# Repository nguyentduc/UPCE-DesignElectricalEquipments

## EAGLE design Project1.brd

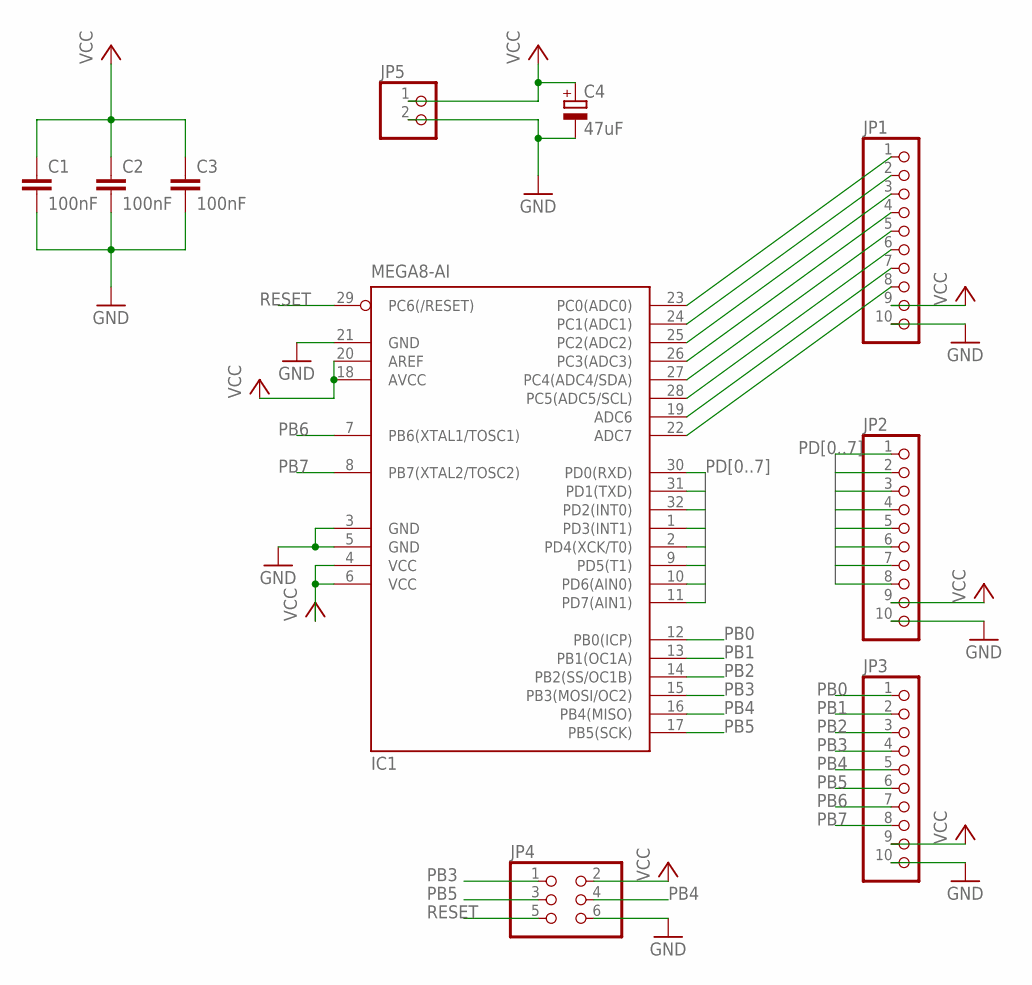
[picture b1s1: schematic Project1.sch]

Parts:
C1, C2, C3: 100nF; C0603
C4: 47uF; E2,5-6
IC1: MEGA8-AI; TQFP32-08
JP1, JP2, JP3: PINHD-1X10; 1X10
JP4: PINHD-2X3; 2X03
JP5: PINHD-1X2; 1X02

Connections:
GND: C1.2, C2.2, C3.2, C4.-, IC1.3 (GND), IC1.5 (GND), IC1.21 (GND), JP1.10, JP2.10, JP3.10, JP4.6, JP5.2
unnamed: IC1.23 (PC0(ADC0)), JP1.1
unnamed: IC1.24 (PC1(ADC1)), JP1.2
unnamed: IC1.25 (PC2(ADC2)), JP1.3
unnamed: IC1.26 (PC3(ADC3)), JP1.4
unnamed: IC1.27 (PC4(ADC4/SDA)), JP1.5
unnamed: IC1.28 (PC5(ADC5/SCL)), JP1.6
unnamed: IC1.19 (ADC6), JP1.7
unnamed: IC1.22 (ADC7), JP1.8
PB0: IC1.12 (PB0(ICP)), JP3.1
PB1: IC1.13 (PB1(OC1A)), JP3.2
PB2: IC1.14 (PB2(SS/OC1B)), JP3.3
PB3: IC1.15 (PB3(MOSI/OC2)), JP3.4, JP4.1
PB4: IC1.16 (PB4(MISO)), JP3.5, JP4.4
PB5: IC1.17 (PB5(SCK)), JP3.6, JP4.3
PB6: IC1.7 (PB6(XTAL1/TOSC1)), JP3.7
PB7: IC1.8 (PB7(XTAL2/TOSC2)), JP3.8
PD0: IC1.30 (PD0(RXD)), JP2.1
PD1: IC1.31 (PD1(TXD)), JP2.2
PD2: IC1.32 (PD2(INT0)), JP2.3
PD3: IC1.1 (PD3(INT1)), JP2.4
PD4: IC1.2 (PD4(XCK/T0)), JP2.5
PD5: IC1.9 (PD5(T1)), JP2.6
PD6: IC1.10 (PD6(AIN0)), JP2.7
PD7: IC1.11 (PD7(AIN1)), JP2.8
RESET: IC1.29 (PC6(/RESET)), JP4.5
VCC: C1.1, C2.1, C3.1, C4.+, IC1.4 (VCC), IC1.6 (VCC), IC1.18 (AVCC), IC1.20 (AREF), JP1.9, JP2.9, JP3.9, JP4.2, JP5.1

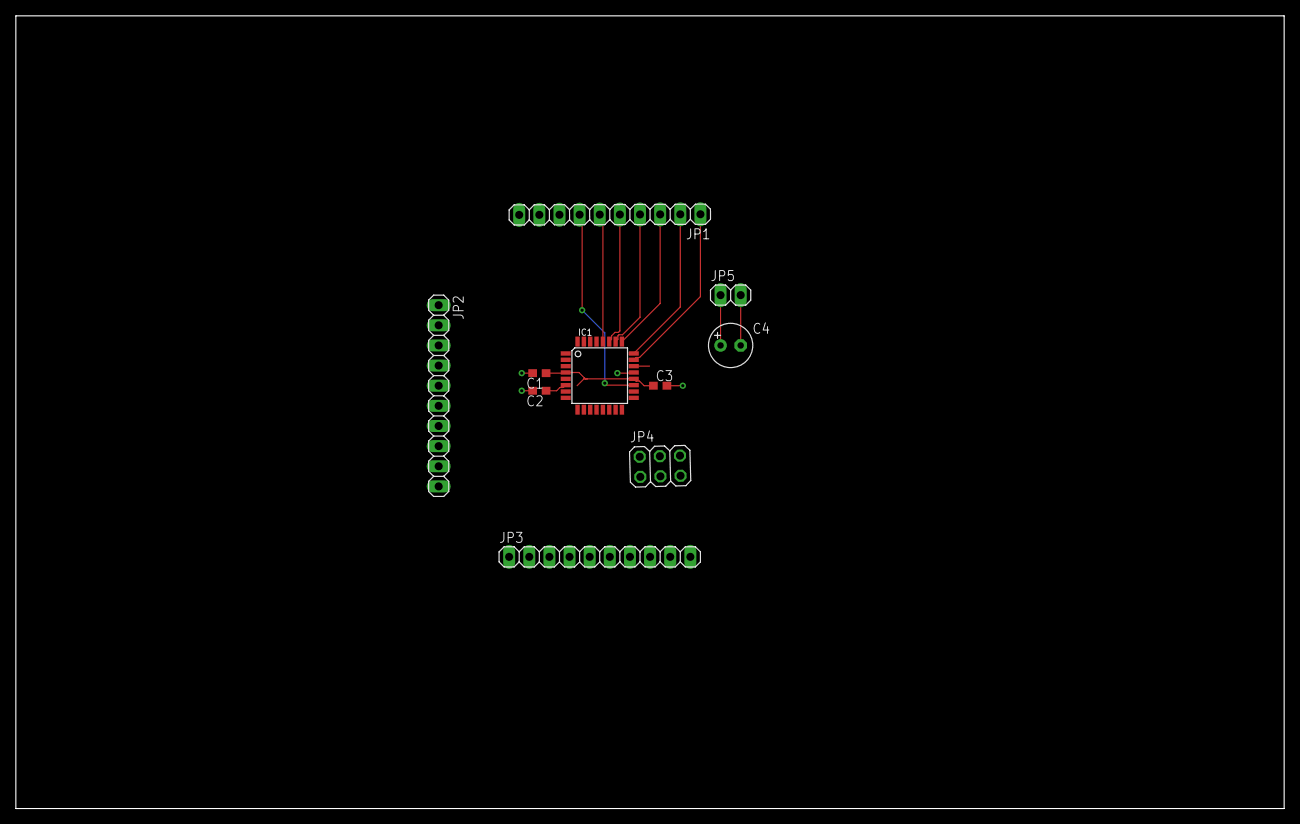
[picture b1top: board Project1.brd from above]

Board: 2 copper layers, 160.0 x 100.0 mm, 10 parts (0 on the bottom side), 26 nets.

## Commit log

2019-04-04 add project schematic
2019-04-04 modified shcamtic, add board
